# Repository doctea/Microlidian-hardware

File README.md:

# Microlidian hardware

- KiCAD files and gerbers for [Microlidian](https://github.com/doctea/Microlidian) eurorack module
- 8hp, 1.14" TFT, 1xTRS MIDI output, 3xbipolar CV input
- NOTE these are not the final files, although it does basically work there are a couple of problems with it, don't use these to make boards without checking with author for a newer version!

## Components

- ST7789 screen "GREATZT 1pcs New IPS 1.14 inch 3.3V 8PIN SPI HD Full Color TFT Display Screen ST7789 Drive IC 135*240": https://www.aliexpress.com/item/4000661571044.html?
- ADS1015 +/-24V ADC breakout by Pimoroni: https://shop.pimoroni.com/products/ads1015-adc-breakout?variant=27859155026003
- Rotary encoder with push button: https://www.amazon.co.uk/gp/product/B07R8JGHB1/ref=pe_3187911_189395841_pd_te_s_rp_im
- Low-profile pin sockets and pin headers for mounting the screen:
  - https://www.aliexpress.com/item/4000920343988.html
  - https://www.aliexpress.com/i/1005004122312694.html

## TODO

### Fixes TODO

- CV in B and C seem to be swapped?
- Mounting holes for the screen need to be bigger on frontboard
- Change frontpanel mounting to fit Type C connector: https://www.aliexpress.com/item/1005004642090483.html
  - (Current one using https://www.aliexpress.com/item/1005003594869227.html has screw holes too small)
- Could provide a little more room for USB cable to come out of the XIAO
- Protection diode on MIDI TRS output to protect MCU pin?
- Protection diode to prevent backpowering rack if a full USB cable is used 
- Change footprint of 78L05 to make it easier to solder cleanly
- Change footprint of the 1uf capacitor as the footprint is too big
- Change footprint of the encoder decoupling capacitors as the footprint is too big
- Don't need the -12v diode
- Add the 47k (check this!) pullups for the encoder left/right
- Why doesn't it restart properly after uploading new code now - runs fine when debugged - seemed to stop working after adding the encoder left/right pullups?

### Possible changes/upgrades

- Replace XIAO with Waveshare RP2040-Zero - has many more pins available for use, so could more easily add MIDI input, CV clock input/outputs, and more buttons
- Could move the screen nearer to the top of the panel, to waste less space

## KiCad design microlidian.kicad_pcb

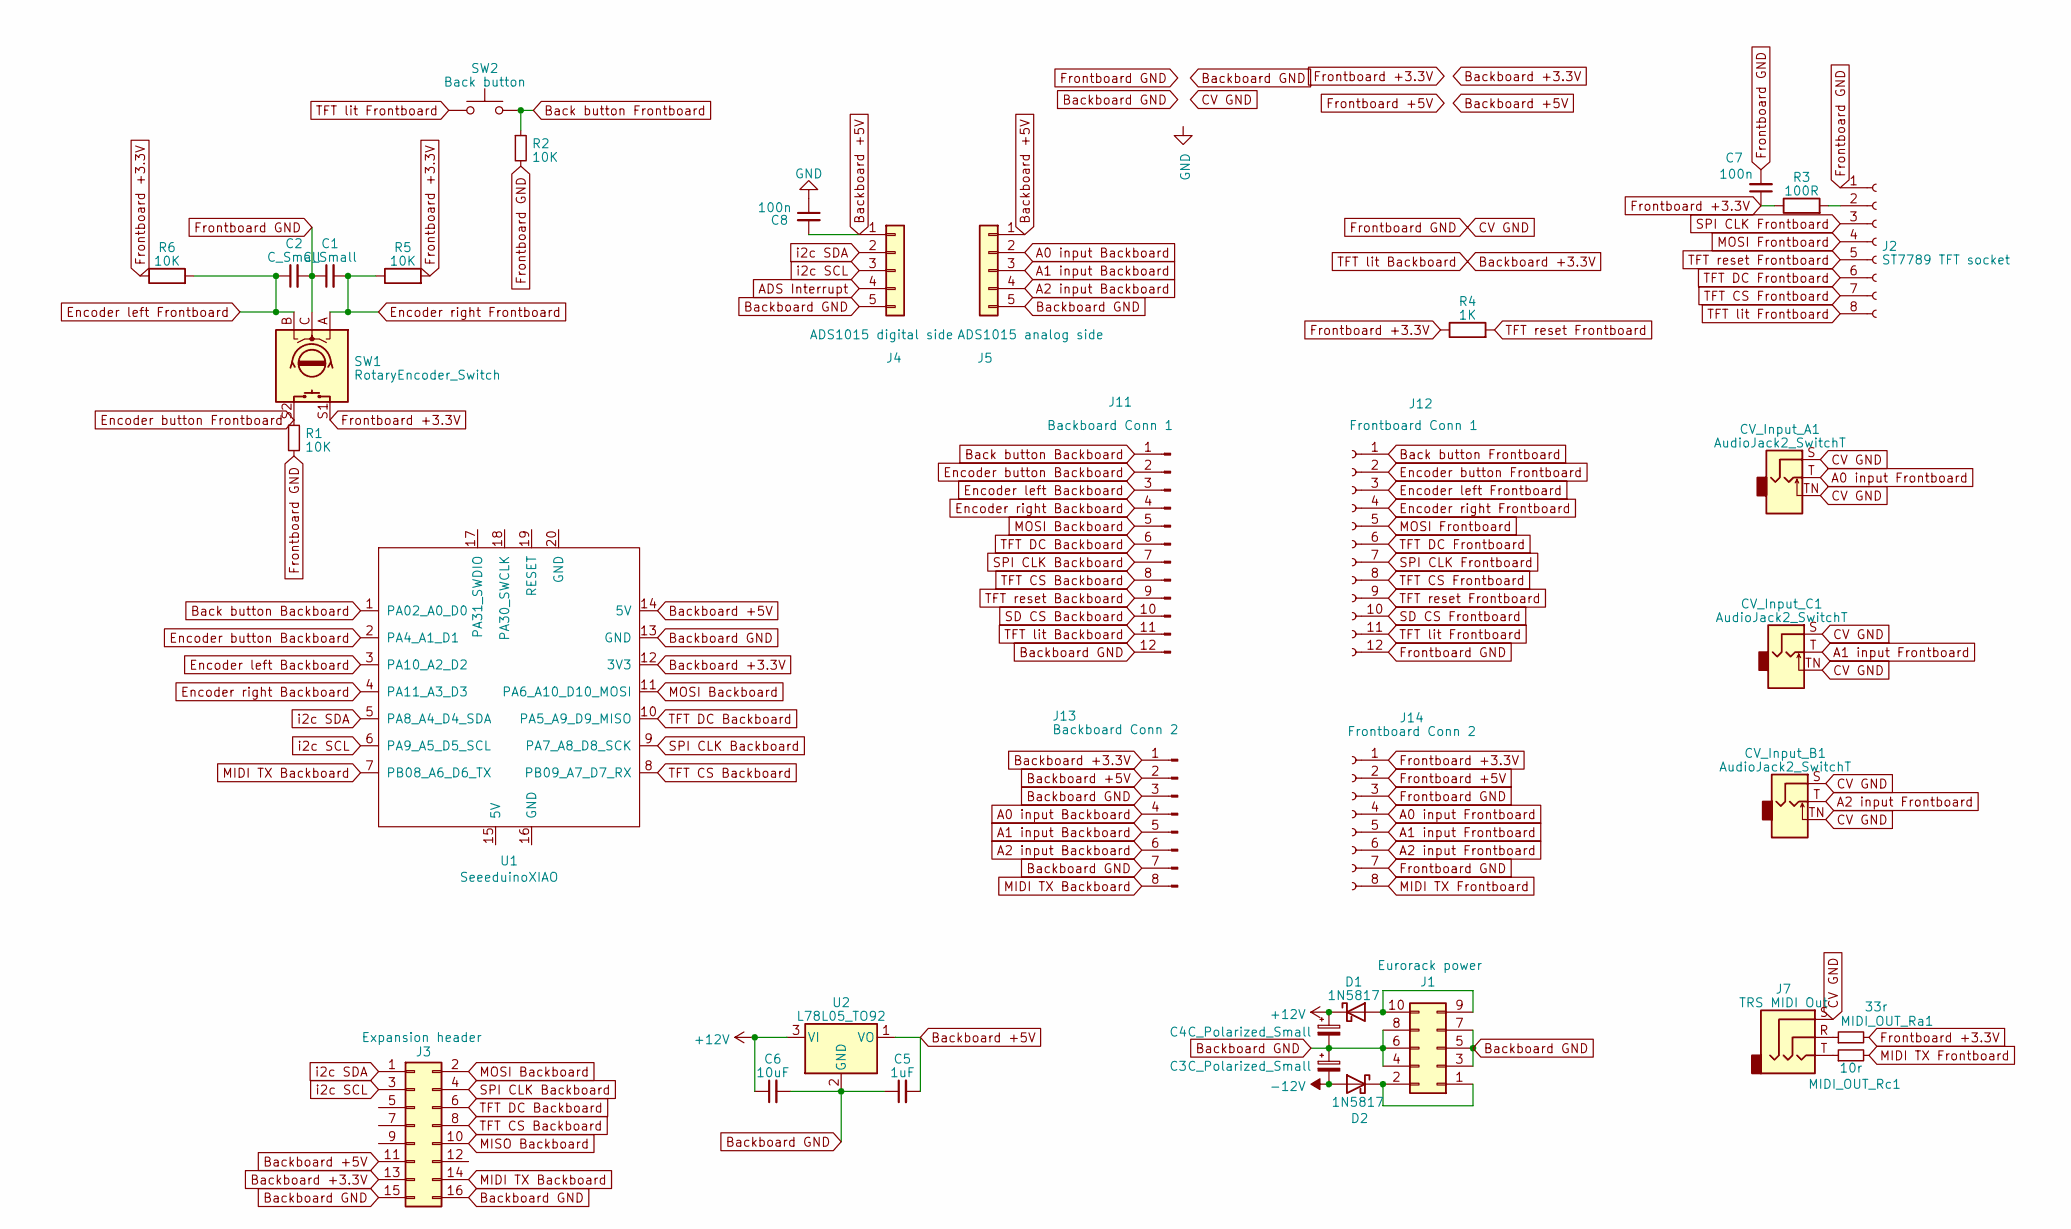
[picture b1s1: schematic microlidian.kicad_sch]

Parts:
C1, C2: C_Small; C_Axial_L3.8mm_D2.6mm_P7.50mm_Horizontal
C3, C4: C_Polarized_Small; CP_Radial_D5.0mm_P2.50mm
C5: 1uF; C_Axial_L3.8mm_D2.6mm_P7.50mm_Horizontal
C6: 10uF; C_Axial_L3.8mm_D2.6mm_P7.50mm_Horizontal
C7, C8: 100n; C_Disc_D5.0mm_W2.5mm_P5.00mm
CV_Input_A1: AudioJack2_SwitchT; Jack_3.5mm_QingPu_WQP-PJ398SM_Vertical_CircularHoles
CV_Input_B1: AudioJack2_SwitchT; Jack_3.5mm_QingPu_WQP-PJ398SM_Vertical_CircularHoles
CV_Input_C1: AudioJack2_SwitchT; Jack_3.5mm_QingPu_WQP-PJ398SM_Vertical_CircularHoles
D1, D2: 1N5817; D_DO-41_SOD81_P10.16mm_Horizontal
J1: Eurorack power; IDC-Header_2x05_P2.54mm_Vertical
J2: ST7789 TFT socket; st7789_1.14_tzt
J3: Expansion header; PinHeader_2x08_P2.54mm_Vertical
J4: ADS1015 digital side; PinSocket_1x05_P2.54mm_Vertical
J5: ADS1015 analog side; PinSocket_1x05_P2.54mm_Vertical
J7: TRS MIDI Out; Jack_3.5mm_QingPu_WQP-PJ398SM_TRS_Vertical_CircularHoles
J11: Backboard Conn 1; PinHeader_1x12_P2.54mm_Vertical
J12: Frontboard Conn 1; PinSocket_1x12_P2.54mm_Vertical
J13: Backboard Conn 2; PinHeader_1x08_P2.54mm_Vertical
J14: Frontboard Conn 2; PinSocket_1x08_P2.54mm_Vertical
MIDI_OUT_Ra1: 33r; R_Axial_DIN0207_L6.3mm_D2.5mm_P7.62mm_Horizontal
MIDI_OUT_Rc1: 10r; R_Axial_DIN0207_L6.3mm_D2.5mm_P7.62mm_Horizontal
R1, R2, R5, R6: 10K; R_Axial_DIN0207_L6.3mm_D2.5mm_P7.62mm_Horizontal
R3: 100R; R_Axial_DIN0207_L6.3mm_D2.5mm_P7.62mm_Horizontal
R4: 1K; R_Axial_DIN0207_L6.3mm_D2.5mm_P7.62mm_Horizontal
SW1: RotaryEncoder_Switch; RotaryEncoder_Alps_EC12E-Switch_Vertical_H20mm
SW2: Back button; SW_PUSH_6mm_H13mm
U1: SeeeduinoXIAO; xiao-tht
U2: L78L05_TO92; TO-92_Inline

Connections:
+12V: C4.1, C6.1, D1.1 (K), U2.3 (VI)
-12V: C3.2, D2.2 (A)
A0 input Backboard: J5.2, J13.4
A0 input Frontboard: CV_Input_A1.T, J14.4
A1 input Backboard: J5.3, J13.5
A1 input Frontboard: CV_Input_C1.T, J14.5
A2 input Backboard: J5.4, J13.6
A2 input Frontboard: CV_Input_B1.T, J14.6
ADS Interrupt: J4.4
Back button Backboard: J11.1, U1.1 (PA02_A0_D0)
Back button Frontboard: J12.1, R2.1, SW2.2
Backboard +3.3V: J3.13, J11.11, J13.1, U1.12 (3V3)
Backboard +5V: C5.2, C8.2, J3.11, J4.1, J5.1, J13.2, U1.14 (5V), U2.1 (VO)
Backboard GND: C3.1, C4.2, C5.1, C6.2, J1.3, J1.4, J1.5, J1.6, J1.7, J1.8, J3.15, J3.16, J4.5, J5.5, J11.12, J13.3, J13.7, U1.13 (GND), U2.2 (GND)
CV GND: C1.1, C2.2, C7.2, CV_Input_A1.S, CV_Input_A1.TN, CV_Input_B1.S, CV_Input_B1.TN, CV_Input_C1.S, CV_Input_C1.TN, J2.1, J7.S, J12.12, J14.3, J14.7, R1.2, R2.2, SW1.C
Encoder button Backboard: J11.2, U1.2 (PA4_A1_D1)
Encoder button Frontboard: J12.2, R1.1, SW1.S2
Encoder left Backboard: J11.3, U1.3 (PA10_A2_D2)
Encoder left Frontboard: C2.1, J12.3, R6.2, SW1.B
Encoder right Backboard: J11.4, U1.4 (PA11_A3_D3)
Encoder right Frontboard: C1.2, J12.4, R5.1, SW1.A
Frontboard +3.3V: C7.1, J14.1, MIDI_OUT_Ra1.2, R3.1, R4.1, R5.2, R6.1, SW1.S1
Frontboard +5V: J14.2
GND: C8.1
MIDI TX Backboard: J3.14, J13.8, U1.7 (PB08_A6_D6_TX)
MIDI TX Frontboard: J14.8, MIDI_OUT_Rc1.2
MISO Backboard: J3.10
MOSI Backboard: J3.2, J11.5, U1.11 (PA6_A10_D10_MOSI)
MOSI Frontboard: J2.4, J12.5
unnamed: D1.2 (A), J1.9, J1.10
unnamed: D2.1 (K), J1.1, J1.2
unnamed: J2.2, R3.2
unnamed: J7.R, MIDI_OUT_Ra1.1
unnamed: J7.T, MIDI_OUT_Rc1.1
SD CS Backboard: J11.10
SD CS Frontboard: J12.10
SPI CLK Backboard: J3.4, J11.7, U1.9 (PA7_A8_D8_SCK)
SPI CLK Frontboard: J2.3, J12.7
TFT CS Backboard: J3.8, J11.8, U1.8 (PB09_A7_D7_RX)
TFT CS Frontboard: J2.7, J12.8
TFT DC Backboard: J3.6, J11.6, U1.10 (PA5_A9_D9_MISO)
TFT DC Frontboard: J2.6, J12.6
TFT lit Frontboard: J2.8, J12.11, SW2.1
TFT reset Backboard: J11.9
TFT reset Frontboard: J2.5, J12.9, R4.2
i2c SCL: J3.3, J4.3, U1.6 (PA9_A5_D5_SCL)
i2c SDA: J3.1, J4.2, U1.5 (PA8_A4_D4_SDA)

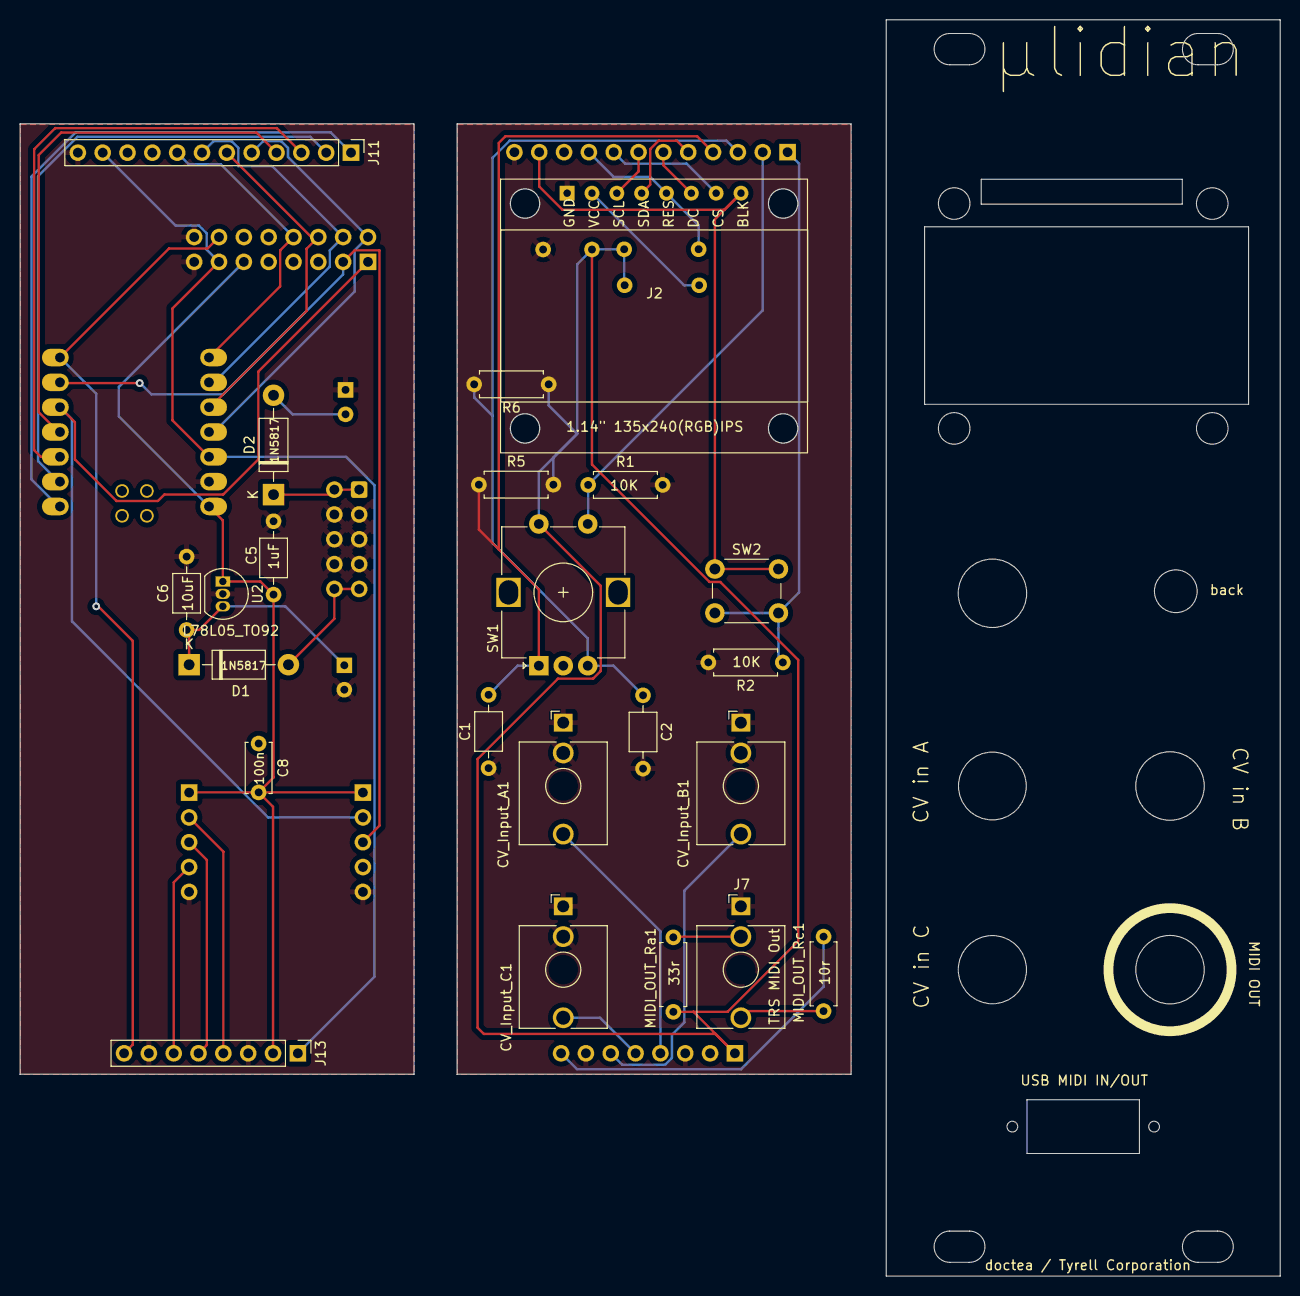
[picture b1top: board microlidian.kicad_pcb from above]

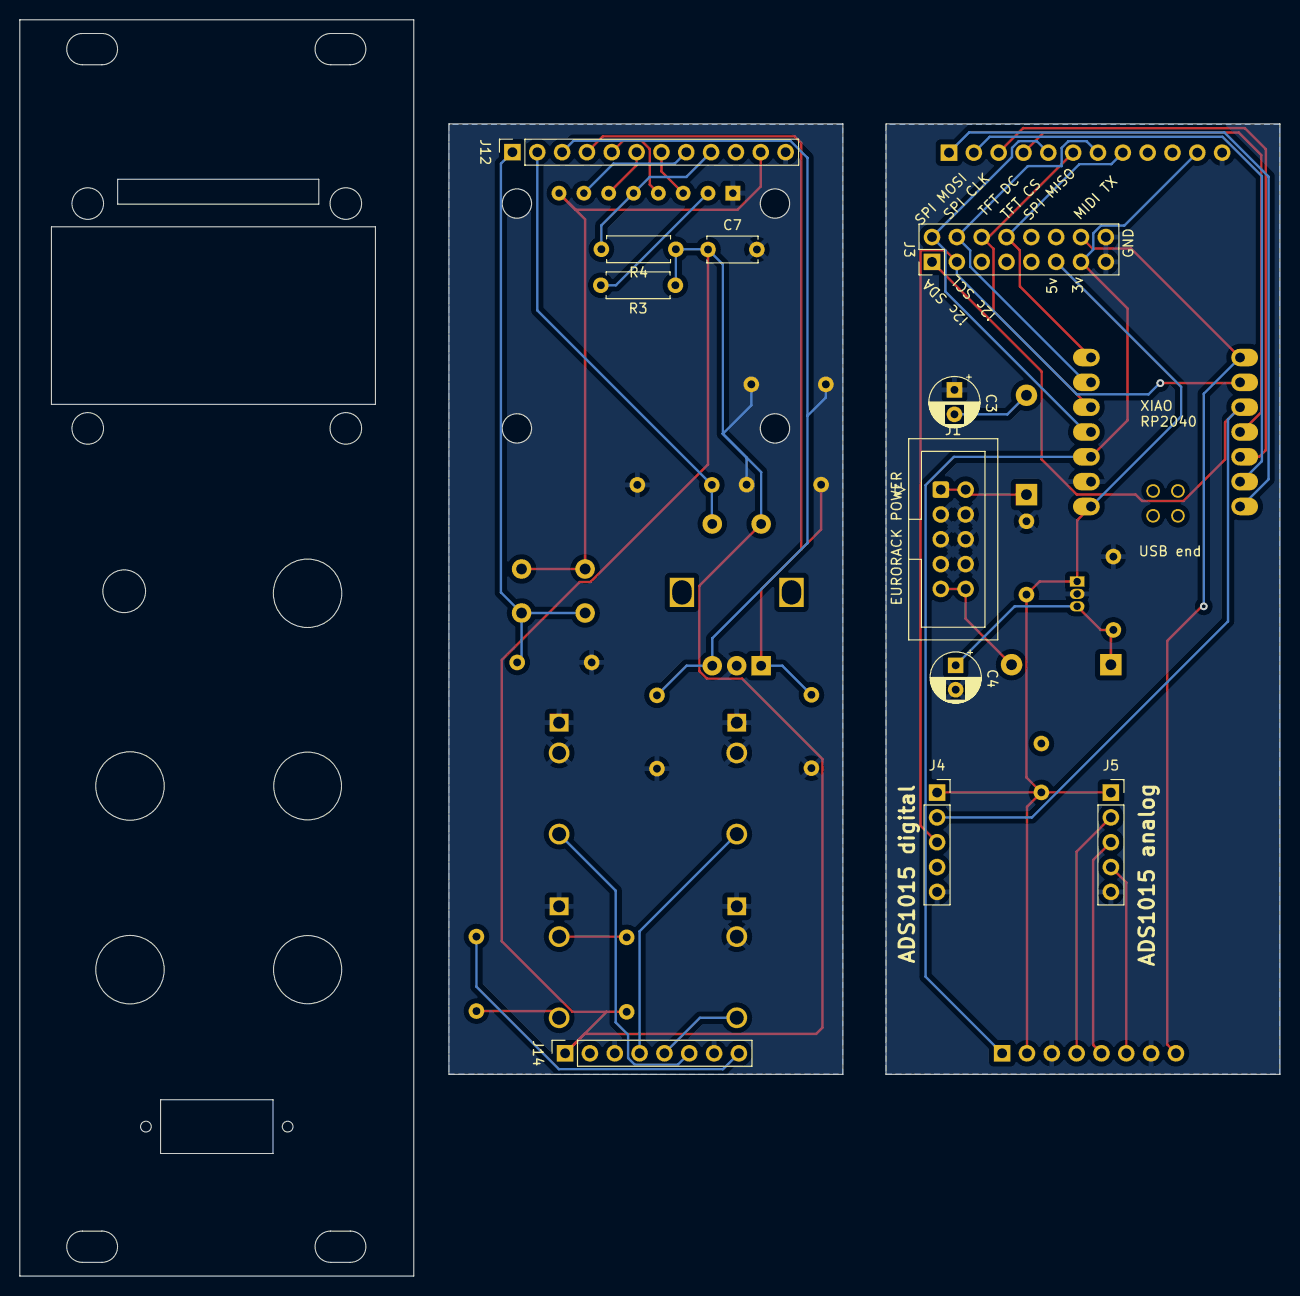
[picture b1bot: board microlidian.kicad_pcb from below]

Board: 2 copper layers, 128.9 x 128.5 mm, 35 parts (12 on the bottom side), 40 nets.

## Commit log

2023-03-14 dunno if this is needed but here it is
2023-03-14 some minor updates
2023-03-15 separated frontboard backboard gnds and +3.3v/+5v. haven't updated pcb at all to match, yet
2023-03-16 updated from schematic, needs to be laid out again
2023-03-19 completely relaid out the pcb
2023-03-19 minor tweaks
2023-03-19 move labels a lil
2023-03-20 separated front/back/panel gerbers
2023-04-03 tracked everything - probably not necessary?
2023-04-03 added readme
2023-04-03 added known problems + todo
2023-05-05 added pullup on RES, think this actually fixes power on screen problem!! :D
2023-05-05 fixed connection to ground
2023-05-05 minor alignment
2023-06-28 updated notes in readme and tracked most recent changes
